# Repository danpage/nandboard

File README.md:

# NANDboard: hands-on Boolean algebra

<!--- -------------------------------------------------------------------- --->

## History

Starting in the 2012/13 academic year, the
[Computer Science Department](http://www.cs.bris.ac.uk)
at the
[University of Bristol](http://www.bris.ac.uk)
changed how the Undergraduate-level, 1st year (or "freshman") Computer
Architecture unit was delivered.  Although it *always* had a practical
emphasis, there was a view it should be even more hands-on.
There were various motivations, included the fact that
a) by doing so the topic could be more engaging,
   but also
b) it seeds an ethos and skills that are of general use: for example,
   it could mean students participate more actively in
   [maker-like](http://en.wikipedia.org/wiki/Maker_culture),
   hardware-based (versus software-only) projects.

The NANDboard, whose original concept and design was due to
[Simon Hollis](https://github.com/simonhollis),
was among various innovations introduced; Simon left at the end of the
2014/15 academic year, ~~prompting~~ forcing me to learn the basics of
PCB design and subsequently revise his initial NANDboard version.

<!--- -------------------------------------------------------------------- --->

## Concept

Although fundamentally important in Computer Science,
[Boolean algebra](http://en.wikipedia.org/wiki/Boolean_algebra)
is a notoriously dry topic.  The problem is exacerbated when hands-on 
experience amounts to solving paper-and-pencil exercises; the typical
result is for students to be increasingly uninterested and disengaged.
The underlying causes are varied, and differ from student to student.
However, anecdotally at least, the following are common:

- There is a disconnection between theory and practice, in the sense
  it is unclear how Boolean algebra directly relates to intuitively 
  useful forms of computation;
  this typically leads to students disengaging,
  based on the view that said theory has no practical use (to them).
- Paper-and-pencil exercises are of a necessarily small scale, which
  can mean 
  [toy problems](http://en.wikipedia.org/wiki/Toy_problem)
  dominate; 
  this typically leads to students disengaging, e.g., because they
  can easily solve said problems so avoid any deeper investigation
  of physical constraints and properties, and unusual designs
  (e.g., a [C-element](https://en.wikipedia.org/wiki/C-element)).
- In part due to the wealth of resources available, modern students 
  are used to and excited by the immediacy of software development;
  this is often direct motivation for studying Computer Science in 
  the first place, with Boolean algebra feeling like a regression 
  towards Mathematics (which, for some, is less popular).

Put another way, this approach is similar, by analogy, to learning
[C](http://en.wikipedia.org/wiki/C_(programming_language))
by studying the language and 
["hello world"](https://en.wikipedia.org/wiki/"Hello,_World!"_program)
style programs *without* ever actually compiling and executing them.

An obvious alternative is to connect theory and practice directly, by
supporting genuinely hands-on, experimental tasks.  One way to do so
might be to equip each student with a breadboard and some
[7400 series](https://en.wikipedia.org/wiki/List_of_7400_series_integrated_circuits)
ICs.  However, for us at least, this presented some problems:
a) large cohort sizes
   (of say 200+ students)
   make the logistics involved quite challenging,
b) said cohorts are typically unfamiliar with, and sometimes have an
   outright dislike for electronics.
The NANDboard attempts to manage these problems.  Conceptually, it is 
just a USB-powered breadboard pre-populated with NAND gates: it could
be viewed as a form of NAND-only
[PLA](http://en.wikipedia.org/wiki/Programmable_logic_array),
where implementation of a Boolean expression (cf. programming the PLA)
amounts to connecting pin headers (i.e., the gate inputs and outputs)
using jumper wire.  There are, of course, some gratuitous
[blinkenlights](http://en.wikipedia.org/wiki/Blinkenlights)
to visualise the inputs and outputs.

<!--- -------------------------------------------------------------------- --->

## Design

Motivated in part by observing how students use them, the NANDboard 
design has gone through several revisions as is illustrated below:

Revision | Image                                                                             | Design                                                                             |
:------: | :-------------------------------------------------------------------------------: | :--------------------------------------------------------------------------------: |
B        |  |                                                                                    |
C        |  |                                                                                    |
D        |  | [files](./rev_d), [schematic](./rev_d/README.pdf), [user guide](./rev_d/README.md) |
F        |  | [files](./rev_f), [schematic](./rev_f/README.pdf), [user guide](./rev_f/README.md) |

<!--- -------------------------------------------------------------------- --->

## Acknowledgements

Later revisions 
(e.g., rev. F) 
were designed and manufactured with generous support from 
[Elliptic Systems](https://elliptic-systems.com).

<!--- -------------------------------------------------------------------- --->

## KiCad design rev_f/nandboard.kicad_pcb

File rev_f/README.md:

<!--- -------------------------------------------------------------------- --->

# High-level structure

At a high level, (the top-side of) a given 
NANDboard
is organised into a set of somewhat groups (or regions) reflected 
by annotation on the 
[PCB](https://en.wikipedia.org/wiki/Printed_circuit_board):

```
+----------+----------+----------+----------+----------+
|    input |     NAND |     NAND |   output |    power |
|    group |    group |    group |    group |    group |
|          |       #0 |       #1 |          |          |
|          +----------+----------+          |          |~~~~ USB
|          |     NAND |     NAND |          |          |
|          |    group |    group |          |          |
|          |       #2 |       #3 |          |          |
+----------+----------+----------+----------+----------+
```

Each group designed to support a specific purpose, as explained
in detail below.  Again
at a high level,
however, use of the 
NANDboard 
can be summarised as follows.  Imagine you are tasked with using 
a
NANDboard
to implement some 4-input, 1-output Boolean function
`R = f( X_0, X_1, X_2, X_3 )`
To do so, the idea is you

- use the  input group  to model (and   control) the  input, 
- use the   NAND groups to implement `f` by decomposing it into a NAND-based expression,
- use the output group  to model (and visualise) the output, 
  
using
[jumper wire](https://en.wikipedia.org/wiki/Jump_wire)
to form connections to inputs, outputs, and between intermediate 
signals.

<!--- -------------------------------------------------------------------- --->

# Low-level detail

### The power    group

Viewed from top-to-bottom,
the  power  group comprises

- an 8x2          [pin header](https://en.wikipedia.org/wiki/Pin_header),
- a type-C [USB](https://en.wikipedia.org/wiki/USB) connector,
- an 8x2          [pin header](https://en.wikipedia.org/wiki/Pin_header).

The basic idea is that:

- The USB connector 
  supplies the 
  NANDboard 
  with power from some host (e.g., a workstation).
- The pin headers allow multiple 
  NANDboards 
  to be
  ["daisy-chained"](https://en.wikipedia.org/wiki/Daisy_chain_(electrical_engineering))
  together, e.g., to implement larger, more complex designs: doing
  so basically means 
  
  - supplying *one*
    "powered"  NANDboard 
    with power via the USB connector
  - supplying *other*
    "tethered" NANDboards
    with power via their pin headers by connecting their
     [5V](https://en.wikipedia.org/wiki/Volt)
    and
    [GND](https://en.wikipedia.org/wiki/Ground_(electricity))
    pins to those of the
    "powered"  NANDboard.

  This demands care, however, because misconnection can potentially 
  damage the board and/or workstation: the safest approach would be
  to cover the pins with
  [jumpers](https://en.wikipedia.org/wiki/Jumper_(computing))
  when not in use.

### The input    group

Viewed from left-to-right, 
the   input group comprises

- 4 [switches](http://en.wikipedia.org/wiki/Switch) (or buttons),
  and
- an 8x2          [pin header](https://en.wikipedia.org/wiki/Pin_header).

so can be thought of conceptually as the following block diagram:
   
```
switches           pins 
 __|__         _____|_____ 
/     \       /           \
               +-----+-----+
+-----+       | X_0 | X_0 |
| X_0 | ~~~>  +-----+-----+
+-----+       | X_0 | X_0 |
              +-----+-----+
+-----+       | X_1 | X_1 |
| X_1 | ~~~>  +-----+-----+
+-----+       | X_1 | X_1 |
              +-----+-----+
+-----+       | X_2 | X_2 |
| X_2 | ~~~>  +-----+-----+
+-----+       | X_2 | X_2 |
              +-----+-----+
+-----+       | X_3 | X_3 |
| X_3 | ~~~>  +-----+-----+
+-----+       | X_3 | X_3 |
              +-----+-----+
```

The basic idea is that
each switch is connected to a group of 4 pins:
the state of each group of pins (i.e., 0 or 1)
is determined by
that of the associated switch,
so when the switch is pressed (resp. not pressed) the pins will be 1 (resp. 0).

### The output   group

Viewed from left-to-right, 
the  output group comprises

- an 8x2          [pin header](https://en.wikipedia.org/wiki/Pin_header),
  and
- 4 [LEDs](https://en.wikipedia.org/wiki/Light-emitting_diode).

```
     pins            LEDs
 _____|_____        __|__
/           \      /     \

+-----+-----+
| R_0 | R_0 |      +-----+
+-----+-----+ ~~~> | R_0 |
| R_0 | R_0 |      +-----+
+-----+-----+
| R_1 | R_1 |      +-----+
+-----+-----+ ~~~> | R_1 | 
| R_1 | R_1 |      +-----+
+-----+-----+
| R_2 | R_2 |      +-----+
+-----+-----+ ~~~> | R_2 |
| R_2 | R_2 |      +-----+
+-----+-----+
| R_3 | R_3 |      +-----+
+-----+-----+ ~~~> | R_3 |
| R_3 | R_3 |      +-----+
+-----+-----+
```

The basic idea is that
each LED    is connected to a group of 4 pins:
the state of each group of pins (i.e., 0 or 1)
determines
that of the associated LED,
so when the pins are 1 (resp. 0) the LED will be on (resp. off).

## The NAND     group(s)

Viewed from left-to-right, 
each NAND   group comprises

- an 4x2 constant [pin header](https://en.wikipedia.org/wiki/Pin_header),
- an 8x2    input [pin header](https://en.wikipedia.org/wiki/Pin_header),
- an [IC](http://www.ti.com/lit/gpn/sn74ac00) that houses 4 [NAND gates](https://en.wikipedia.org/wiki/NAND_gate),
- an 8x2   output [pin header](https://en.wikipedia.org/wiki/Pin_header).
  and
- 4 [LEDs](https://en.wikipedia.org/wiki/Light-emitting_diode).

so can be thought of conceptually as the following block diagram:

```
constant pins
 _____|_____
/           \

+-----+-----+
|  1  |  1  |
+-----+-----+
|  1  |  1  |
+-----+-----+

 input pins                NAND gates             output pins         LEDs
 _____|_____        ___________|__________        _____|_____        __|__
/           \      /                      \      /           \      /     \

+-----+-----+      +----------------------+      +-----+-----+
| x_0 | x_0 | ~~~> |                      |      | r_0 | r_0 |      +-----+
+-----+-----+      | r_0 = ~( x_0 & y_0 ) | ~~~> +-----+-----+ ~~~> | r_0 |
| y_0 | y_0 | ~~~> |                      |      | r_0 | r_0 |      +-----+
+-----+-----+      |                      |      +-----+-----+
| x_1 | x_1 | ~~~> |                      |      | r_1 | r_1 |      +-----+
+-----+-----+      | r_1 = ~( x_1 & y_1 ) | ~~~> +-----+-----+ ~~~> | r_1 |
| y_1 | y_1 | ~~~> |                      |      | r_1 | r_1 |      +-----+
+-----+-----+      |                      |      +-----+-----+
| x_2 | x_2 | ~~~> |                      |      | r_2 | r_2 |      +-----+
+-----+-----+      | r_2 = ~( x_2 & y_2 ) | ~~~> +-----+-----+ ~~~> | r_2 |
| y_2 | y_2 | ~~~> |                      |      | r_2 | r_2 |      +-----+
+-----+-----+      |                      |      +-----+-----+
| x_3 | x_3 | ~~~> |                      |      | r_3 | r_3 |      +-----+
+-----+-----+      | r_3 = ~( x_3 & y_3 ) | ~~~> +-----+-----+ ~~~> | r_3 |
| y_3 | y_3 | ~~~> |                      |      | r_3 | r_3 |      +-----+
+-----+-----+      +----------------------+      +-----+-----+
```
   
The basic idea is that:

- Each group houses 4 replicated instances of the same structure,
  the `i`-th of which computes 
  `r_i = ~( x_i & y_i )`.
  We use on the 0-th, top-most instance as an example throughout
  the following.  

- The computation of
  `r_0 = ~( x_0 & y_0 )`
  relates to the top 4 pins (i.e., top 2 rows) of both the input
  and output pins headers: the input pins marked `x_0` and `y_0` 
  provided an input to the NAND gate, which produces a result 
  reflected on the output pins marked `r_0`.  
  Each output pin is also connected to an LED, allowing the state
  (i.e., 0 or 1) to be visualised.

- Note there are 2 pins marked `x_0` and `y_0` on the input pin
  header: since they are connected together, either of the 2 pins
  (i.e., the left- *or* right-hand pin marked `x_0`) can be used 
  to provide the associated input.  Likewise, there are 4 pins
  marked `r_0` on the output pin header: the NAND gate output is
  replicated on each of those pins.

- Each input pin is 
  [pulled-down](http://en.wikipedia.org/wiki/Pull-up_resistor), 
  meaning that `x_0` and `y_0` are 0 and `r_0` is 1 by default.
  However, an input pin can be freely connected (via jumper wire)
  to any other

  - constant           pin,
  - input group        pin,
  - NAND  group input  pin,
  - NAND  group output pin

  elsewhere on the NANDboard.

- Since each input pin is 0-by-default, the constant pins can be
  used to "override" this.  Imagine that rather than
  `r_0 = ~( x_0 & y_0 )`,
  you need to compute
  `r_0 = ~( x_0 & 1   )`
  for some reason: a reasonable approach is to connect the `y_0` 
  input pin of the NAND gate to one of the 1-by-default constant
  pins.

- The NAND groups and hence operators are independent, meaning 
  you can form inter- and intra-group connections (i.e., inside 
  one group and between two groups).

### Misc.

The bottom-side of the
NANDboard
includes a
10-pin [TagConnect](https://www.tag-connect.com)
header: those pins connect to

- the 
  [5V](https://en.wikipedia.org/wiki/Volt)
  and
  [GND](https://en.wikipedia.org/wiki/Ground_(electricity))
  pins in the  power group,
- each 
  pin  in the  input group, i.e., `X_0`, `X_1`, `X_2`, and `X_3`,
  and
- each 
  pin  in the output group, i.e., `R_0`, `R_1`, `R_2`, and `R_3`.

By connecting the
NANDboard
to a host using a compliant
[pogo-pin](https://en.wikipedia.org/wiki/Pogo_pin) 
style cable, one can therefore programmatically control input to
and inspect output generated by it; an example use-case would be
to automatically, and exhaustively test whether the
NANDboard 
correctly implements a given function.

<!--- -------------------------------------------------------------------- --->

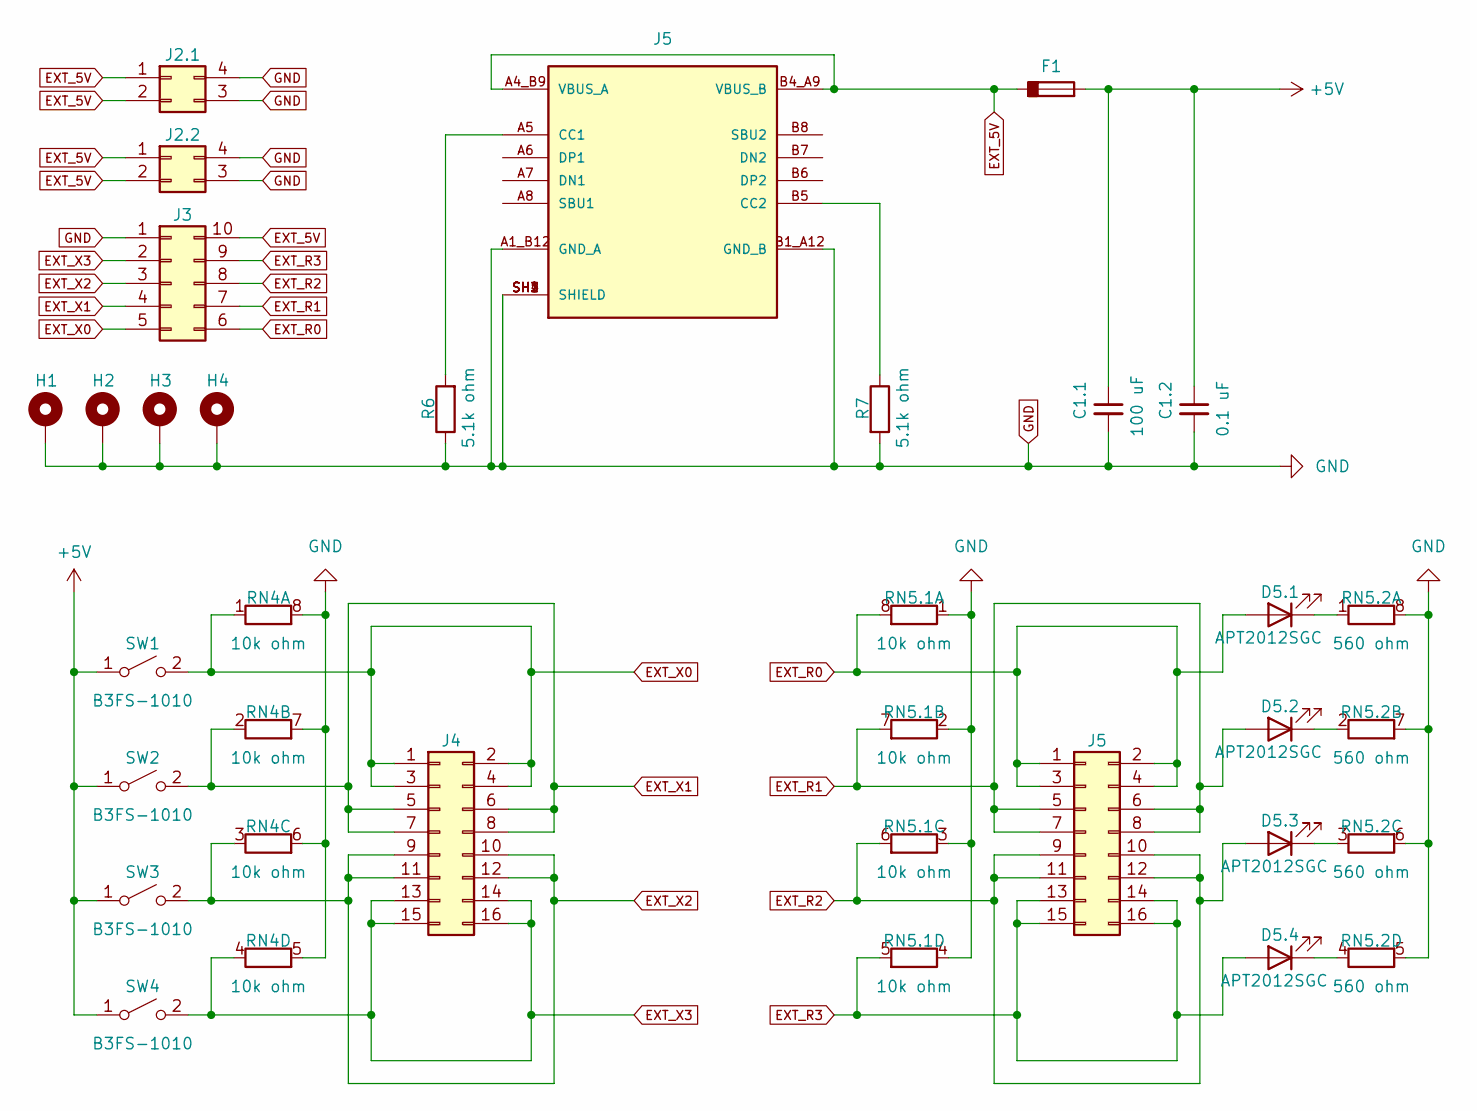
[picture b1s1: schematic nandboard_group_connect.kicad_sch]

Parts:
C1.1: 100 uF; C_1210_3225Metric
C1.2: 0.1 uF; C_0805_2012Metric
D5.1, D5.2, D5.3, D5.4: APT2012SGC; LED_0805_2012Metric
F1: Fuse_Polarized; Fuse_1206_3216Metric
H1, H2, H3, H4: MountingHole_Pad; MountingHole_3.2mm_M3_Pad
J2.1, J2.2: Conn_02x02_Counter_Clockwise; PinHeader_2x02_P2.54mm_Vertical_SMD
J3: Conn_02x05_Counter_Clockwise; Tag-Connect_TC2050-IDC-NL_2x05_P1.27mm_Vertical
J4: Conn_02x08_Odd_Even; PinHeader_2x08_P2.54mm_Vertical_SMD
J5: USB_C_Receptacle_USB2.0; AMPHENOL_GSB1C41110SSHR; Mouser Part Number 523-GSB1C41110SSHR
R6, R7: 5.1k ohm; R_0603_1608Metric; Mouser Part Number 755-SFR18EZPF5101
RN4, RN5.1: 10k ohm; RN-1206-Convex-LongSideTerminals
RN5.2: 560 ohm; RN-1206-Convex-LongSideTerminals
SW1, SW2, SW3, SW4: B3FS-1010; SW_SPST_Omron_B3FS-101xP

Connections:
+5V: C1.1.1, C1.2.1, F1.2, SW1.1 (A), SW2.1 (A), SW3.1 (A), SW4.1 (A); also elsewhere on the board
EXT_5V: F1.1, J2.1.1, J2.1.2, J2.2.1, J2.2.2, J3.10, J5.A4_B9 (VBUS_A), J5.B4_A9 (VBUS_B); also elsewhere on the board
EXT_R0: D5.1.2 (A), J3.6, J5.1, J5.2, J5.3, J5.4, RN5.1.8 (R1.2)
EXT_R1: D5.2.2 (A), J3.7, J5.5, J5.6, J5.7, J5.8, RN5.1.7 (R2.2)
EXT_R2: D5.3.2 (A), J3.8, J5.9, J5.10, J5.11, J5.12, RN5.1.6 (R3.2)
EXT_R3: D5.4.2 (A), J3.9, J5.13, J5.14, J5.15, J5.16, RN5.1.5 (R4.2)
EXT_X0: J3.5, J4.1, J4.2, J4.3, J4.4, RN4.1 (R1.1), SW1.2 (B)
EXT_X1: J3.4, J4.5, J4.6, J4.7, J4.8, RN4.2 (R2.1), SW2.2 (B)
EXT_X2: J3.3, J4.9, J4.10, J4.11, J4.12, RN4.3 (R3.1), SW3.2 (B)
EXT_X3: J3.2, J4.13, J4.14, J4.15, J4.16, RN4.4 (R4.1), SW4.2 (B)
GND: C1.1.2, C1.2.2, H1.1, H2.1, H3.1, H4.1, J2.1.3, J2.1.4, J2.2.3, J2.2.4, J3.1, J5.A1_B12 (GND_A), J5.B1_A12 (GND_B), J5.SH1 (SHIELD), J5.SH2 (SHIELD), J5.SH3 (SHIELD), J5.SH4 (SHIELD), RN4.5 (R4.2), RN4.6 (R3.2), RN4.7 (R2.2), RN4.8 (R1.2), RN5.1.1 (R1.1), RN5.1.2 (R2.1), RN5.1.3 (R3.1), RN5.1.4 (R4.1), RN5.2.5 (R4.2), RN5.2.6 (R3.2), RN5.2.7 (R2.2), RN5.2.8 (R1.2); also elsewhere on the board
unnamed: D5.1.1 (K), RN5.2.1 (R1.1)
unnamed: D5.2.1 (K), RN5.2.2 (R2.1)
unnamed: D5.3.1 (K), RN5.2.3 (R3.1)
unnamed: D5.4.1 (K), RN5.2.4 (R4.1)

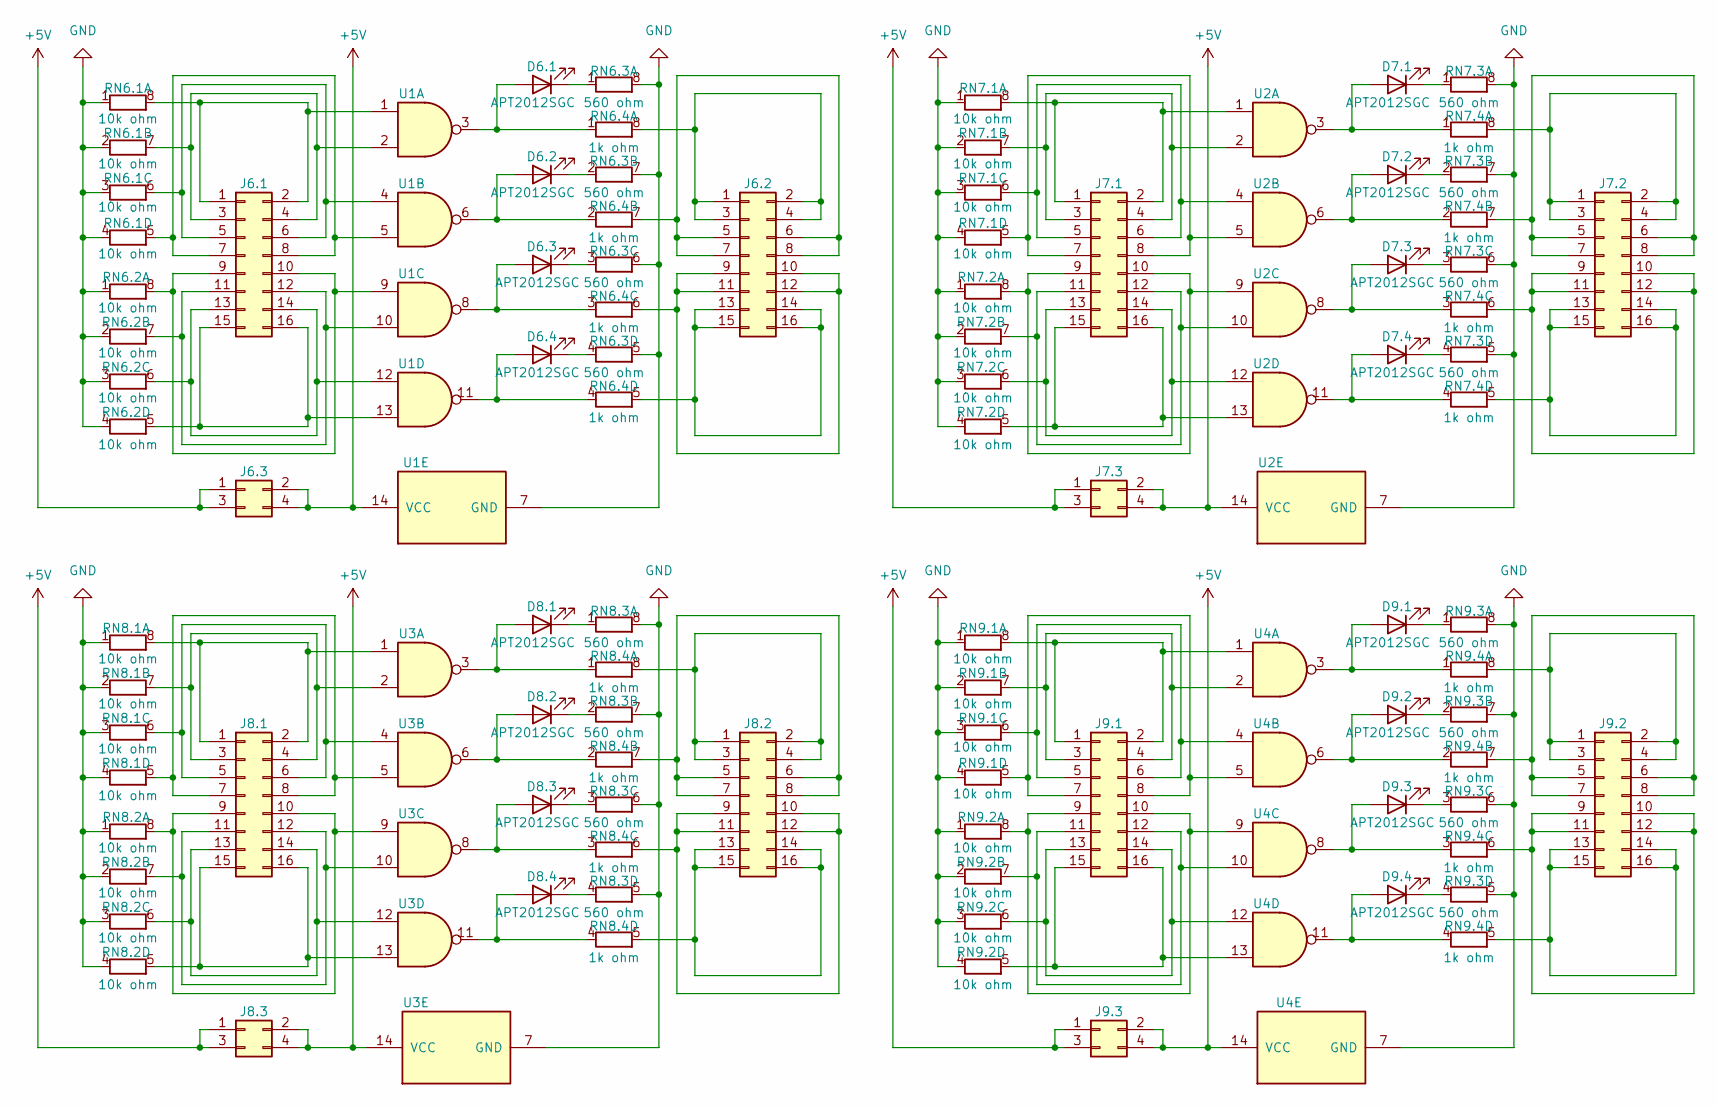
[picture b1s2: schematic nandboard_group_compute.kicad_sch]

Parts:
D6.1, D6.2, D6.3, D6.4, D7.1, D7.2, D7.3, D7.4, D8.1, D8.2, D8.3, D8.4, D9.1, D9.2, D9.3, D9.4: APT2012SGC; LED_0805_2012Metric
J6.1, J6.2, J7.1, J7.2, J8.1, J8.2, J9.1, J9.2: Conn_02x08_Odd_Even; PinHeader_2x08_P2.54mm_Vertical_SMD
J6.3, J7.3, J8.3, J9.3: Conn_02x02_Odd_Even; PinHeader_2x02_P2.54mm_Vertical_SMD
RN6.1, RN6.2, RN7.1, RN7.2, RN8.1, RN8.2, RN9.1, RN9.2: 10k ohm; RN-1206-Convex-LongSideTerminals
RN6.3, RN7.3, RN8.3, RN9.3: 560 ohm; RN-1206-Convex-LongSideTerminals
RN6.4, RN7.4, RN8.4, RN9.4: 1k ohm; RN-1206-Convex-LongSideTerminals
U1, U2, U3, U4: 7400; SOIC-14_3.9x8.7mm_P1.27mm

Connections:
+5V: J6.3.1, J6.3.2, J6.3.3, J6.3.4, J7.3.1, J7.3.2, J7.3.3, J7.3.4, J8.3.1, J8.3.2, J8.3.3, J8.3.4, J9.3.1, J9.3.2, J9.3.3, J9.3.4, U1.14 (VCC), U2.14 (VCC), U3.14 (VCC), U4.14 (VCC); also elsewhere on the board
GND: RN6.1.1 (R1.1), RN6.1.2 (R2.1), RN6.1.3 (R3.1), RN6.1.4 (R4.1), RN6.2.1 (R1.1), RN6.2.2 (R2.1), RN6.2.3 (R3.1), RN6.2.4 (R4.1), RN6.3.5 (R4.2), RN6.3.6 (R3.2), RN6.3.7 (R2.2), RN6.3.8 (R1.2), RN7.1.1 (R1.1), RN7.1.2 (R2.1), RN7.1.3 (R3.1), RN7.1.4 (R4.1), RN7.2.1 (R1.1), RN7.2.2 (R2.1), RN7.2.3 (R3.1), RN7.2.4 (R4.1), RN7.3.5 (R4.2), RN7.3.6 (R3.2), RN7.3.7 (R2.2), RN7.3.8 (R1.2), RN8.1.1 (R1.1), RN8.1.2 (R2.1), RN8.1.3 (R3.1), RN8.1.4 (R4.1), RN8.2.1 (R1.1), RN8.2.2 (R2.1), RN8.2.3 (R3.1), RN8.2.4 (R4.1), RN8.3.5 (R4.2), RN8.3.6 (R3.2), RN8.3.7 (R2.2), RN8.3.8 (R1.2), RN9.1.1 (R1.1), RN9.1.2 (R2.1), RN9.1.3 (R3.1), RN9.1.4 (R4.1), RN9.2.1 (R1.1), RN9.2.2 (R2.1), RN9.2.3 (R3.1), RN9.2.4 (R4.1), RN9.3.5 (R4.2), RN9.3.6 (R3.2), RN9.3.7 (R2.2), RN9.3.8 (R1.2), U1.7 (GND), U2.7 (GND), U3.7 (GND), U4.7 (GND); also elsewhere on the board
unnamed: D6.1.2 (A), RN6.4.1 (R1.1), U1.3
unnamed: D6.1.1 (K), RN6.3.1 (R1.1)
unnamed: D6.2.2 (A), RN6.4.2 (R2.1), U1.6
unnamed: D6.2.1 (K), RN6.3.2 (R2.1)
unnamed: D6.3.2 (A), RN6.4.3 (R3.1), U1.8
unnamed: D6.3.1 (K), RN6.3.3 (R3.1)
unnamed: D6.4.2 (A), RN6.4.4 (R4.1), U1.11
unnamed: D6.4.1 (K), RN6.3.4 (R4.1)
unnamed: D7.1.2 (A), RN7.4.1 (R1.1), U2.3
unnamed: D7.1.1 (K), RN7.3.1 (R1.1)
unnamed: D7.2.2 (A), RN7.4.2 (R2.1), U2.6
unnamed: D7.2.1 (K), RN7.3.2 (R2.1)
unnamed: D7.3.2 (A), RN7.4.3 (R3.1), U2.8
unnamed: D7.3.1 (K), RN7.3.3 (R3.1)
unnamed: D7.4.2 (A), RN7.4.4 (R4.1), U2.11
unnamed: D7.4.1 (K), RN7.3.4 (R4.1)
unnamed: D8.1.2 (A), RN8.4.1 (R1.1), U3.3
unnamed: D8.1.1 (K), RN8.3.1 (R1.1)
unnamed: D8.2.2 (A), RN8.4.2 (R2.1), U3.6
unnamed: D8.2.1 (K), RN8.3.2 (R2.1)
unnamed: D8.3.2 (A), RN8.4.3 (R3.1), U3.8
unnamed: D8.3.1 (K), RN8.3.3 (R3.1)
unnamed: D8.4.2 (A), RN8.4.4 (R4.1), U3.11
unnamed: D8.4.1 (K), RN8.3.4 (R4.1)
unnamed: D9.1.2 (A), RN9.4.1 (R1.1), U4.3
unnamed: D9.1.1 (K), RN9.3.1 (R1.1)
unnamed: D9.2.2 (A), RN9.4.2 (R2.1), U4.6
unnamed: D9.2.1 (K), RN9.3.2 (R2.1)
unnamed: D9.3.2 (A), RN9.4.3 (R3.1), U4.8
unnamed: D9.3.1 (K), RN9.3.3 (R3.1)
unnamed: D9.4.2 (A), RN9.4.4 (R4.1), U4.11
unnamed: D9.4.1 (K), RN9.3.4 (R4.1)
unnamed: J6.1.1, J6.1.2, RN6.1.8 (R1.2), U1.1
unnamed: J6.1.3, J6.1.4, RN6.1.7 (R2.2), U1.2
unnamed: J6.1.5, J6.1.6, RN6.1.6 (R3.2), U1.4
unnamed: J6.1.7, J6.1.8, RN6.1.5 (R4.2), U1.5
unnamed: J6.1.9, J6.1.10, RN6.2.8 (R1.2), U1.9
unnamed: J6.1.11, J6.1.12, RN6.2.7 (R2.2), U1.10
unnamed: J6.1.13, J6.1.14, RN6.2.6 (R3.2), U1.12
unnamed: J6.1.15, J6.1.16, RN6.2.5 (R4.2), U1.13
unnamed: J6.2.1, J6.2.2, J6.2.3, J6.2.4, RN6.4.8 (R1.2)
unnamed: J6.2.5, J6.2.6, J6.2.7, J6.2.8, RN6.4.7 (R2.2)
unnamed: J6.2.9, J6.2.10, J6.2.11, J6.2.12, RN6.4.6 (R3.2)
unnamed: J6.2.13, J6.2.14, J6.2.15, J6.2.16, RN6.4.5 (R4.2)
unnamed: J7.1.1, J7.1.2, RN7.1.8 (R1.2), U2.1
unnamed: J7.1.3, J7.1.4, RN7.1.7 (R2.2), U2.2
unnamed: J7.1.5, J7.1.6, RN7.1.6 (R3.2), U2.4
unnamed: J7.1.7, J7.1.8, RN7.1.5 (R4.2), U2.5
unnamed: J7.1.9, J7.1.10, RN7.2.8 (R1.2), U2.9
unnamed: J7.1.11, J7.1.12, RN7.2.7 (R2.2), U2.10
unnamed: J7.1.13, J7.1.14, RN7.2.6 (R3.2), U2.12
unnamed: J7.1.15, J7.1.16, RN7.2.5 (R4.2), U2.13
unnamed: J7.2.1, J7.2.2, J7.2.3, J7.2.4, RN7.4.8 (R1.2)
unnamed: J7.2.5, J7.2.6, J7.2.7, J7.2.8, RN7.4.7 (R2.2)
unnamed: J7.2.9, J7.2.10, J7.2.11, J7.2.12, RN7.4.6 (R3.2)
unnamed: J7.2.13, J7.2.14, J7.2.15, J7.2.16, RN7.4.5 (R4.2)
unnamed: J8.1.1, J8.1.2, RN8.1.8 (R1.2), U3.1
unnamed: J8.1.3, J8.1.4, RN8.1.7 (R2.2), U3.2
unnamed: J8.1.5, J8.1.6, RN8.1.6 (R3.2), U3.4
unnamed: J8.1.7, J8.1.8, RN8.1.5 (R4.2), U3.5
unnamed: J8.1.9, J8.1.10, RN8.2.8 (R1.2), U3.9
unnamed: J8.1.11, J8.1.12, RN8.2.7 (R2.2), U3.10
unnamed: J8.1.13, J8.1.14, RN8.2.6 (R3.2), U3.12
unnamed: J8.1.15, J8.1.16, RN8.2.5 (R4.2), U3.13
unnamed: J8.2.1, J8.2.2, J8.2.3, J8.2.4, RN8.4.8 (R1.2)
unnamed: J8.2.5, J8.2.6, J8.2.7, J8.2.8, RN8.4.7 (R2.2)
unnamed: J8.2.9, J8.2.10, J8.2.11, J8.2.12, RN8.4.6 (R3.2)
unnamed: J8.2.13, J8.2.14, J8.2.15, J8.2.16, RN8.4.5 (R4.2)
unnamed: J9.1.1, J9.1.2, RN9.1.8 (R1.2), U4.1
unnamed: J9.1.3, J9.1.4, RN9.1.7 (R2.2), U4.2
unnamed: J9.1.5, J9.1.6, RN9.1.6 (R3.2), U4.4
unnamed: J9.1.7, J9.1.8, RN9.1.5 (R4.2), U4.5
unnamed: J9.1.9, J9.1.10, RN9.2.8 (R1.2), U4.9
unnamed: J9.1.11, J9.1.12, RN9.2.7 (R2.2), U4.10
unnamed: J9.1.13, J9.1.14, RN9.2.6 (R3.2), U4.12
unnamed: J9.1.15, J9.1.16, RN9.2.5 (R4.2), U4.13
unnamed: J9.2.1, J9.2.2, J9.2.3, J9.2.4, RN9.4.8 (R1.2)
unnamed: J9.2.5, J9.2.6, J9.2.7, J9.2.8, RN9.4.7 (R2.2)
unnamed: J9.2.9, J9.2.10, J9.2.11, J9.2.12, RN9.4.6 (R3.2)
unnamed: J9.2.13, J9.2.14, J9.2.15, J9.2.16, RN9.4.5 (R4.2)

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
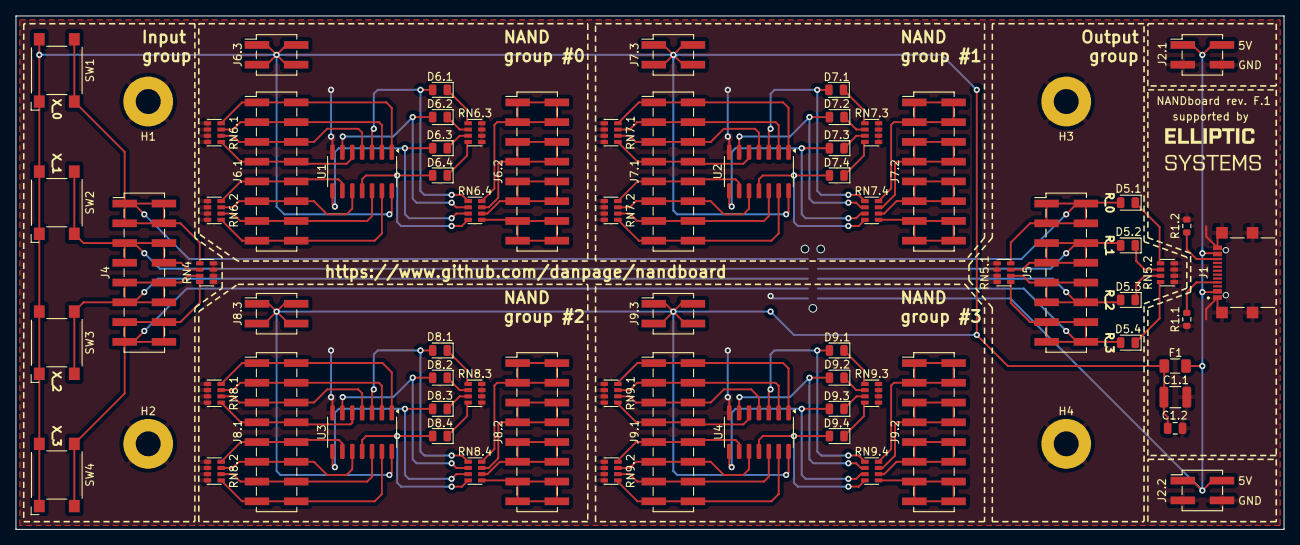
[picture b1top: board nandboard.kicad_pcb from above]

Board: 2 copper layers, 163.0 x 66.0 mm, 74 parts (1 on the bottom side), 97 nets.

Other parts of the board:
J1: USB_C_Receptacle_USB2.0; AMPHENOL_GSB1C41110SSHR
R1.1, R1.2: 5.1k ohm; R_0603_1608Metric

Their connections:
EXT_5V: J1.A4_B9 (VBUS_A), J1.B4_A9 (VBUS_B); also elsewhere on the board
GND: J1.A1_B12 (GND_A), J1.B1_A12 (GND_B), J1.SH1 (SHIELD), J1.SH2 (SHIELD), J1.SH3 (SHIELD), J1.SH4 (SHIELD), R1.1.1, R1.2.2; also elsewhere on the board

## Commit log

2015-10-05 initial commit of rev. D design, plus fleshed out README.txt etc.
2017-04-12 updated to rev. E design, moved to Octopart-based BOM, improved README.md
2017-04-12 clean-up of older files
2017-04-13 fixed a couple of markdown glitches
2017-07-06 updated README.md to include OSH Park PCB link
2017-07-20 added CSV-based BOMs (replicating Octopart BOM offline)
2017-08-16 reorganised design files; improved photography a little
2017-08-16 fixed typo. in image path
2018-05-31 fixed typos in URLs; added schematic PDFs
2018-05-31 move PDFs to LFS-based storage
2021-11-09 Update README.md
    https://forum.kicad.info/t/warning-avoid-all-links-to-kicad-pcb-org-use-kicad-org/31521
2024-09-02 start work on content for rev_f
2024-09-09 bump
2024-09-13 add rev. F; remove rev. E; restructure user guide(s); rewrite PDF generator(s)
2024-09-20 update PCB photo with better version
2025-01-07 update URL for Simon from (dead) CS -> GitHub
